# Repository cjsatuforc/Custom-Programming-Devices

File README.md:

# Custom Programming Devices

A collection of useful little helper boards and layouts.

#### FTDI USB Friend
A board derived from the Adafruit FTDI Friend. Uses the Mini-USB conductors to program an ATMega328. Ignores CTS Pin for that sake.

#### Mini USB Breakout
Exactly what it sounds like

#### Programming Headers
Special ISP Headers for Pogo Pins that allow for minimal routes and make it easier to create single-sided PCBs.
Matching Parts in my eagle library.

#### USB FTDI Connector
Similar to the FTDI USB Friend - but allows one to use standard FTDI Board.

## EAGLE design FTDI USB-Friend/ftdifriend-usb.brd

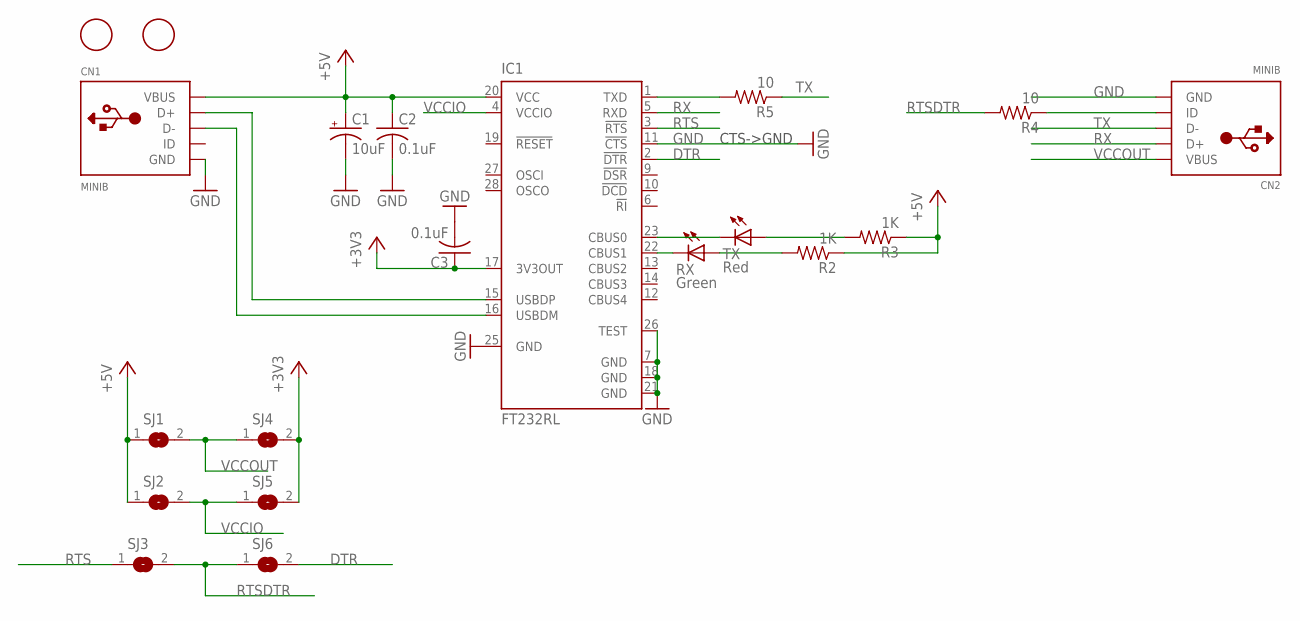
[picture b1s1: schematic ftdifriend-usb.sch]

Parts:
C1: 10uF; A/3216-18R
C2, C3: 0.1uF; C0805K
CN1, CN2: MINIB; USB-MINIB
IC1: FT232RL; SSOP28
R2, R3: 1K; R0805
R4, R5: 10; R0805
RX: Green; CHIP-LED0805
SJ1, SJ2, SJ3, SJ4, SJ5, SJ6: SJ
TX: Red; CHIP-LED0805
U$1, U$2: FIDUCIAL; FIDUCIAL_1MM

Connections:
1: CN2.ID, R4.1
+3V3: C3.1, IC1.17 (3V3OUT), SJ4.2, SJ5.2
+5V: C1.+, C2.1, CN1.VBUS, IC1.20 (VCC), R2.1, R3.1, SJ1.1, SJ2.1
DTR: IC1.2 (!DTR), SJ6.2
GND: C1.-, C2.2, C3.2, CN1.GND, CN2.GND, IC1.7 (GND), IC1.11 (!CTS), IC1.18 (GND), IC1.21 (GND), IC1.25 (GND), IC1.26 (TEST)
unnamed: CN1.D+, IC1.15 (USBDP)
unnamed: CN1.D-, IC1.16 (USBDM)
unnamed: IC1.1 (TXD), R5.2
unnamed: IC1.23 (CBUS0), TX.C
unnamed: IC1.22 (CBUS1), RX.C
unnamed: R2.2, RX.A
unnamed: R3.2, TX.A
RTS: IC1.3 (!RTS), SJ3.1
RTSDTR: R4.2, SJ3.2, SJ6.1
RX: CN2.D+, IC1.5 (RXD)
TX: CN2.D-, R5.1
VCCIO: IC1.4 (VCCIO), SJ2.2, SJ5.1
VCCOUT: CN2.VBUS, SJ1.2, SJ4.1

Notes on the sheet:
CTS->GND

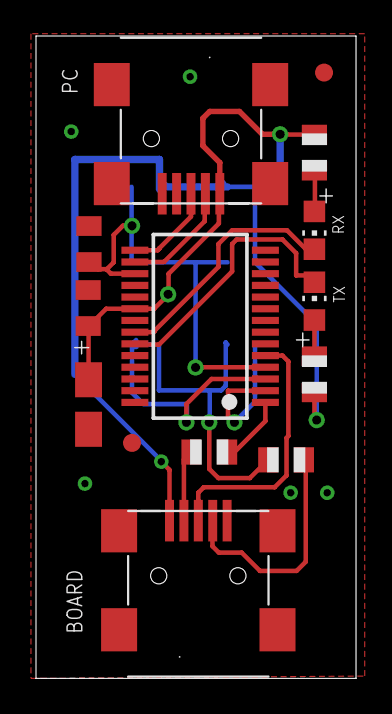
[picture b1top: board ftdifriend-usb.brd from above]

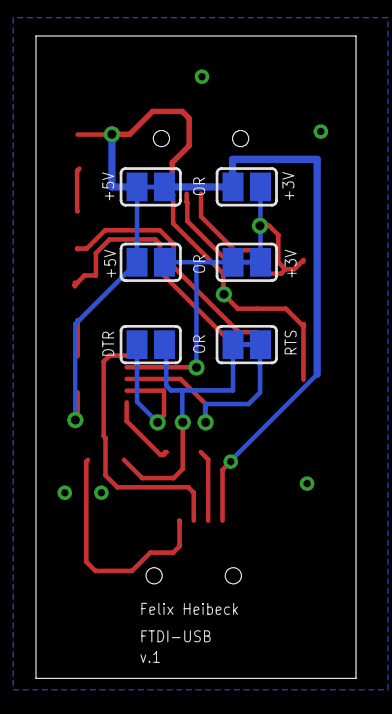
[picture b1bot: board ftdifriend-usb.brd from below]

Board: 2 copper layers, 17.8 x 35.7 mm, 20 parts (6 on the bottom side), 18 nets.

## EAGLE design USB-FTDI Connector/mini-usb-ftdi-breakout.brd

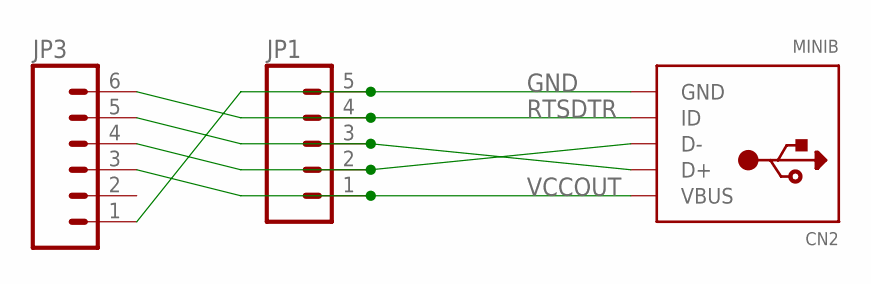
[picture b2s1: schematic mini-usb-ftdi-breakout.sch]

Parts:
CN2: MINIB; USB-MINIB
JP1: M05PTH; 1X05
JP3: M06SMD; 1X06-SMD

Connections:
GND: CN2.GND, JP1.5, JP3.1
unnamed: CN2.D+, JP1.3, JP3.5
unnamed: CN2.D-, JP1.2, JP3.4
RTSDTR: CN2.ID, JP1.4, JP3.6
VCCOUT: CN2.VBUS, JP1.1, JP3.3

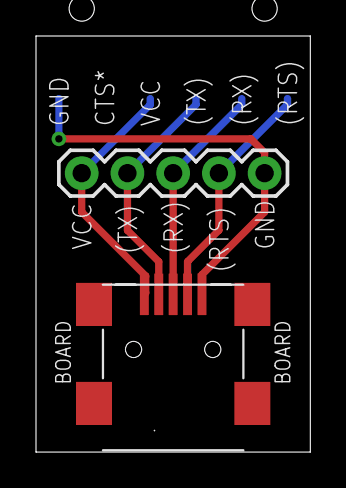
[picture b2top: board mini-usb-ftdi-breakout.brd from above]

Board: 2 copper layers, 15.2 x 23.1 mm, 3 parts (1 on the bottom side), 5 nets.

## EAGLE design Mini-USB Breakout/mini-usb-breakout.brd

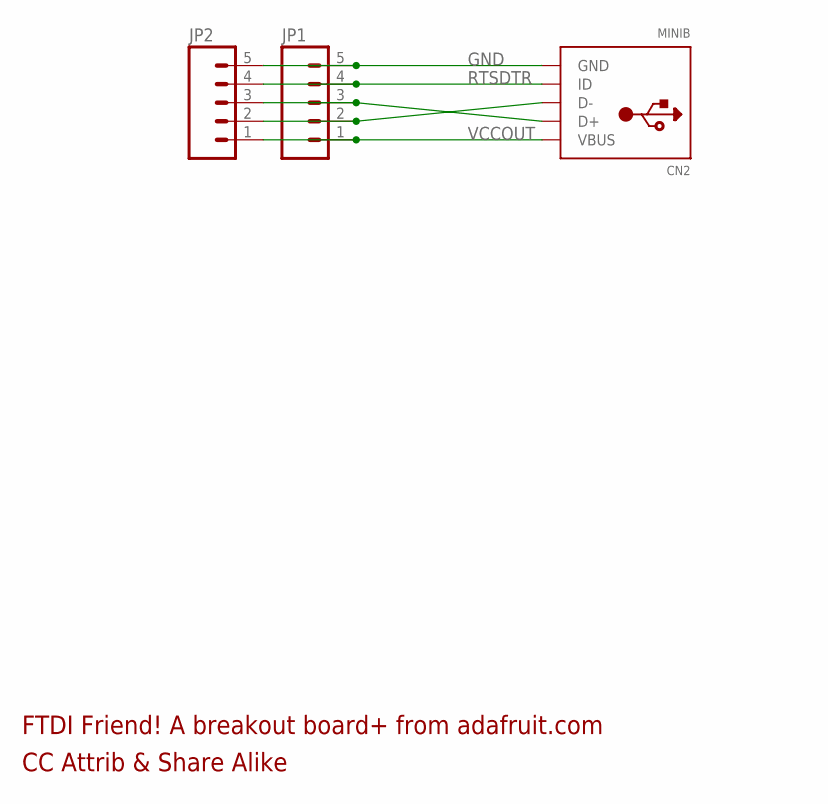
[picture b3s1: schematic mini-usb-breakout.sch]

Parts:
CN2: MINIB; USB-MINIB
JP1, JP2: M05PTH; 1X05

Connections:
GND: CN2.GND, JP1.5, JP2.5
unnamed: CN2.D+, JP1.3, JP2.3
unnamed: CN2.D-, JP1.2, JP2.2
RTSDTR: CN2.ID, JP1.4, JP2.4
VCCOUT: CN2.VBUS, JP1.1, JP2.1

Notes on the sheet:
CC Attrib & Share Alike
FTDI Friend! A breakout board+ from adafruit.com

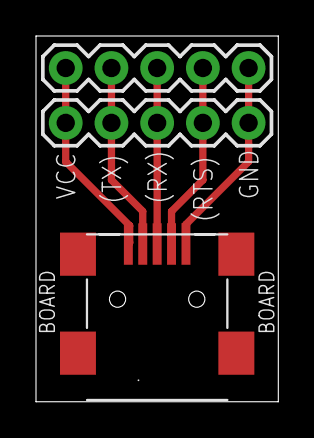
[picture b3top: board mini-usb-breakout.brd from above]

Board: 2 copper layers, 13.5 x 20.3 mm, 3 parts (0 on the bottom side), 5 nets.

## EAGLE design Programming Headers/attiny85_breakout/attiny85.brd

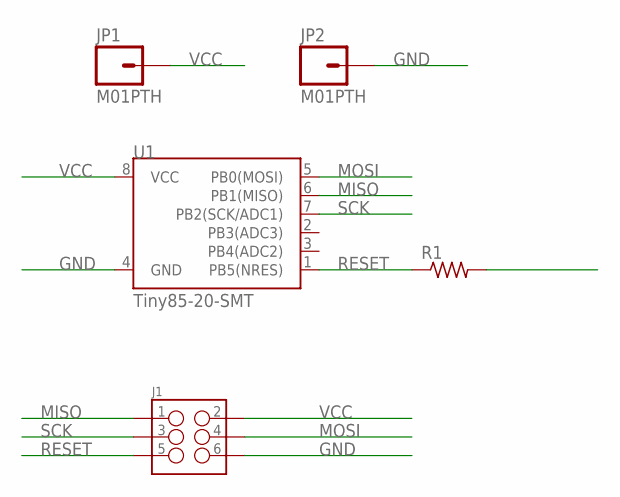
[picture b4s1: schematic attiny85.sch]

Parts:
J1: M03X2SMT; 2X3_SMT_POSTS
JP1, JP2: M01PTH; 1X01
R1: R-US_M0805; M0805
U1: Tiny85-20-SMT; SO08-EIAJ

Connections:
GND: J1.6, JP2.1, U1.4 (GND)
MISO: J1.1, U1.6 (PB1(MISO))
MOSI: J1.4, U1.5 (PB0(MOSI))
RESET: J1.5, R1.1, U1.1 (PB5(NRES))
SCK: J1.3, U1.7 (PB2(SCK/ADC1))
VCC: J1.2, JP1.1, R1.2, U1.8 (VCC)

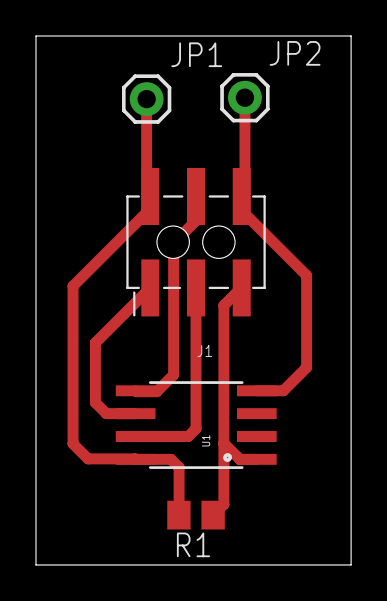
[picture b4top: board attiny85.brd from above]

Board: 2 copper layers, 17.5 x 29.4 mm, 5 parts (0 on the bottom side), 6 nets.

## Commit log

2015-02-18 create
2015-03-13 small changes

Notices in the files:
parts and their libraries:
SparkFun-Connectors: Licensing: Creative Commons ShareAlike 4.0 International - https://creativecommons.org/licenses/by-sa/4.0
SparkFun-Connectors: Licensing: CC v3.0 Share-Alike You are welcome to use this library for commercial purposes.
